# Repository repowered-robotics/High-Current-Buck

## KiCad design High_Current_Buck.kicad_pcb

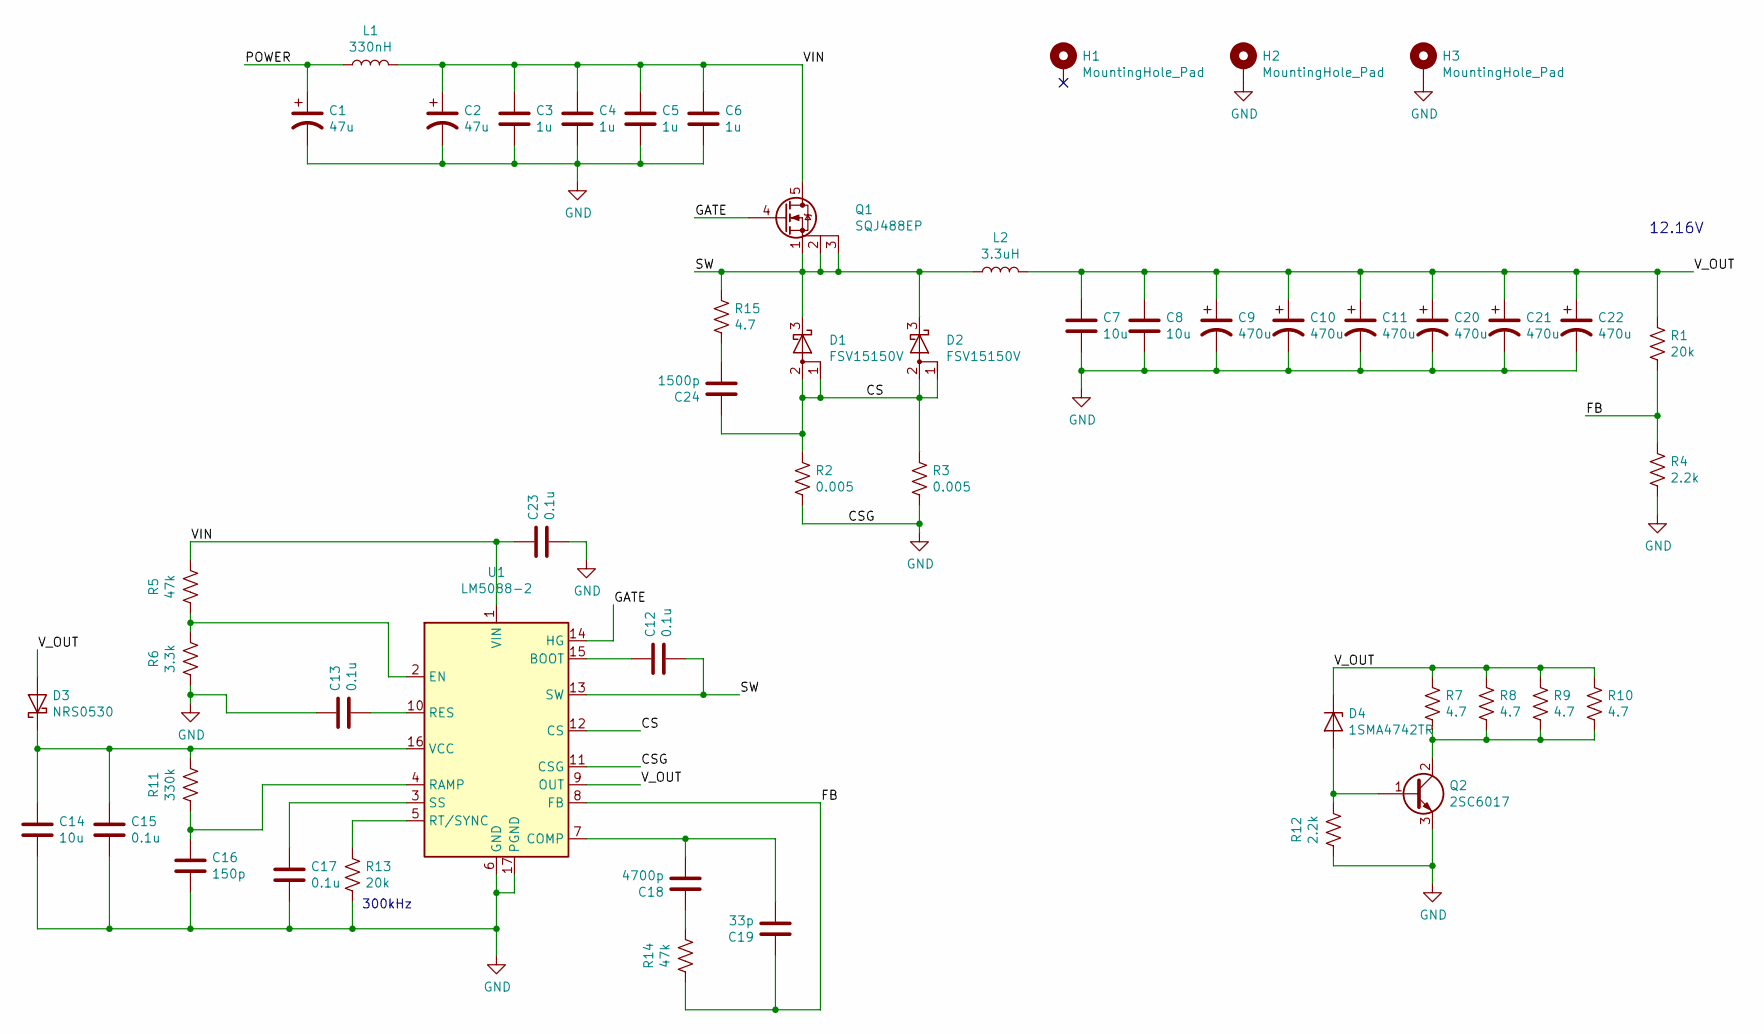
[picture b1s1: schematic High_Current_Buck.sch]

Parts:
C1, C2: 47u; CP_Radial_D12.5mm_P5.00mm
C3, C4, C5, C6: 1u; C_1206_3216Metric
C7, C8, C14: 10u; C_1206_3216Metric
C9, C10, C11, C20, C21, C22: 470u; CP_Radial_D12.5mm_P5.00mm
C12: 0.1u; C_0805_2012Metric
C13, C15, C17, C23: 0.1u; C_0603_1608Metric
C16: 150p; C_0603_1608Metric
C18: 4700p; C_0603_1608Metric
C19: 33p; C_0603_1608Metric
C24: 1500p; C_0805_2012Metric
D1, D2: FSV15150V; TO-277A
D3: NRS0530; D_SOD-323
D4: 1SMA4742TR; D_SMA
H1, H2, H3: MountingHole_Pad; MountingHole_3.7mm_Pad
L1: 330nH; L_Vishay_IHLP-3232
L2: 3.3uH; L_Wuerth_HCI-2212
Q1: SQJ488EP; PowerPAK_SO-8L_Single
Q2: 2SC6017; TO-252-2
R1, R13: 20k; R_0603_1608Metric
R2, R3: 0.005; R_2512_6332Metric
R4, R12: 2.2k; R_0603_1608Metric
R5, R14: 47k; R_0603_1608Metric
R6: 3.3k; R_0603_1608Metric
R7, R8, R9, R10, R15: 4.7; R_2512_6332Metric
R11: 330k; R_0603_1608Metric
U1: LM5088-2; HTSSOP-16-1EP_4.4x5mm_P0.65mm_EP3.4x5mm_Mask3x3mm_ThermalVi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

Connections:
/CS: C24.1, D1.1 (A), D1.2 (A), D2.1 (A), D2.2 (A), R2.1, R3.1, U1.12 (CS)
/FB: C19.1, R1.2, R4.1, R14.1, U1.8 (FB)
/GATE: Q1.4 (G), U1.14 (HG)
/POWER: C1.1, L1.1
/SW: C12.2, D1.3 (K), D2.3 (K), L2.1, Q1.1 (S), Q1.2 (S), Q1.3 (S), R15.1, U1.13 (SW)
/VIN: C2.1, C3.1, C4.1, C5.1, C6.1, C23.1, L1.2, Q1.5 (D), R5.2, U1.1 (VIN)
/V_OUT: C7.1, C8.1, C9.1, C10.1, C11.1, C20.1, C21.1, C22.1, D3.2 (A), D4.1 (K), L2.2, R1.1, R7.1, R8.1, R9.1, R10.1, U1.9 (OUT)
GND: C1.2, C2.2, C3.2, C4.2, C5.2, C6.2, C7.2, C8.2, C9.2, C10.2, C11.2, C13.1, C14.2, C15.2, C16.2, C17.2, C20.2, C21.2, C22.2, C23.2, H2.1, H3.1, Q2.3 (E), R2.2, R3.2, R4.2, R6.1, R12.1, R13.2, U1.6 (GND), U1.11 (CSG), U1.17 (PGND)
unnamed: C12.1, U1.15 (BOOT)
unnamed: C13.2, U1.10 (RES)
unnamed: C14.1, C15.1, D3.1 (K), R11.2, U1.16 (VCC)
unnamed: C16.1, R11.1, U1.4 (RAMP)
unnamed: C17.1, U1.3 (SS)
unnamed: C18.1, R14.2
unnamed: C18.2, C19.2, U1.7 (COMP)
unnamed: C24.2, R15.2
unnamed: D4.2 (A), Q2.1 (B), R12.2
unnamed: Q2.2 (C), R7.2, R8.2, R9.2, R10.2
unnamed: R5.1, R6.2, U1.2 (EN)
unnamed: R13.1, U1.5 (RT/SYNC)

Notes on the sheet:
300kHz
12.16V

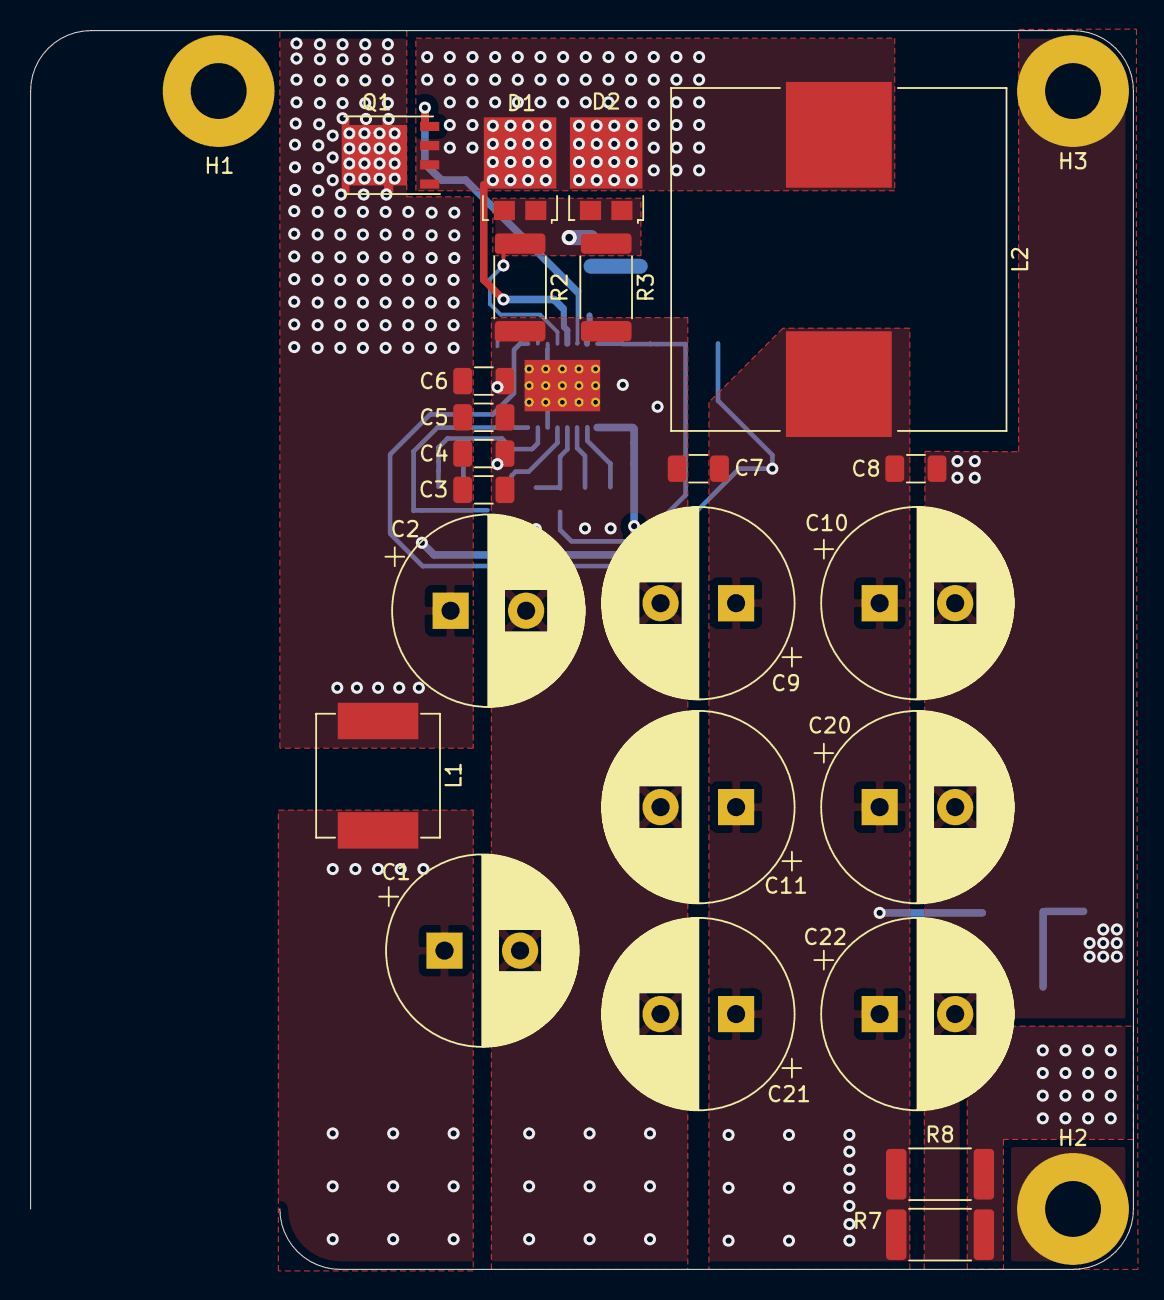
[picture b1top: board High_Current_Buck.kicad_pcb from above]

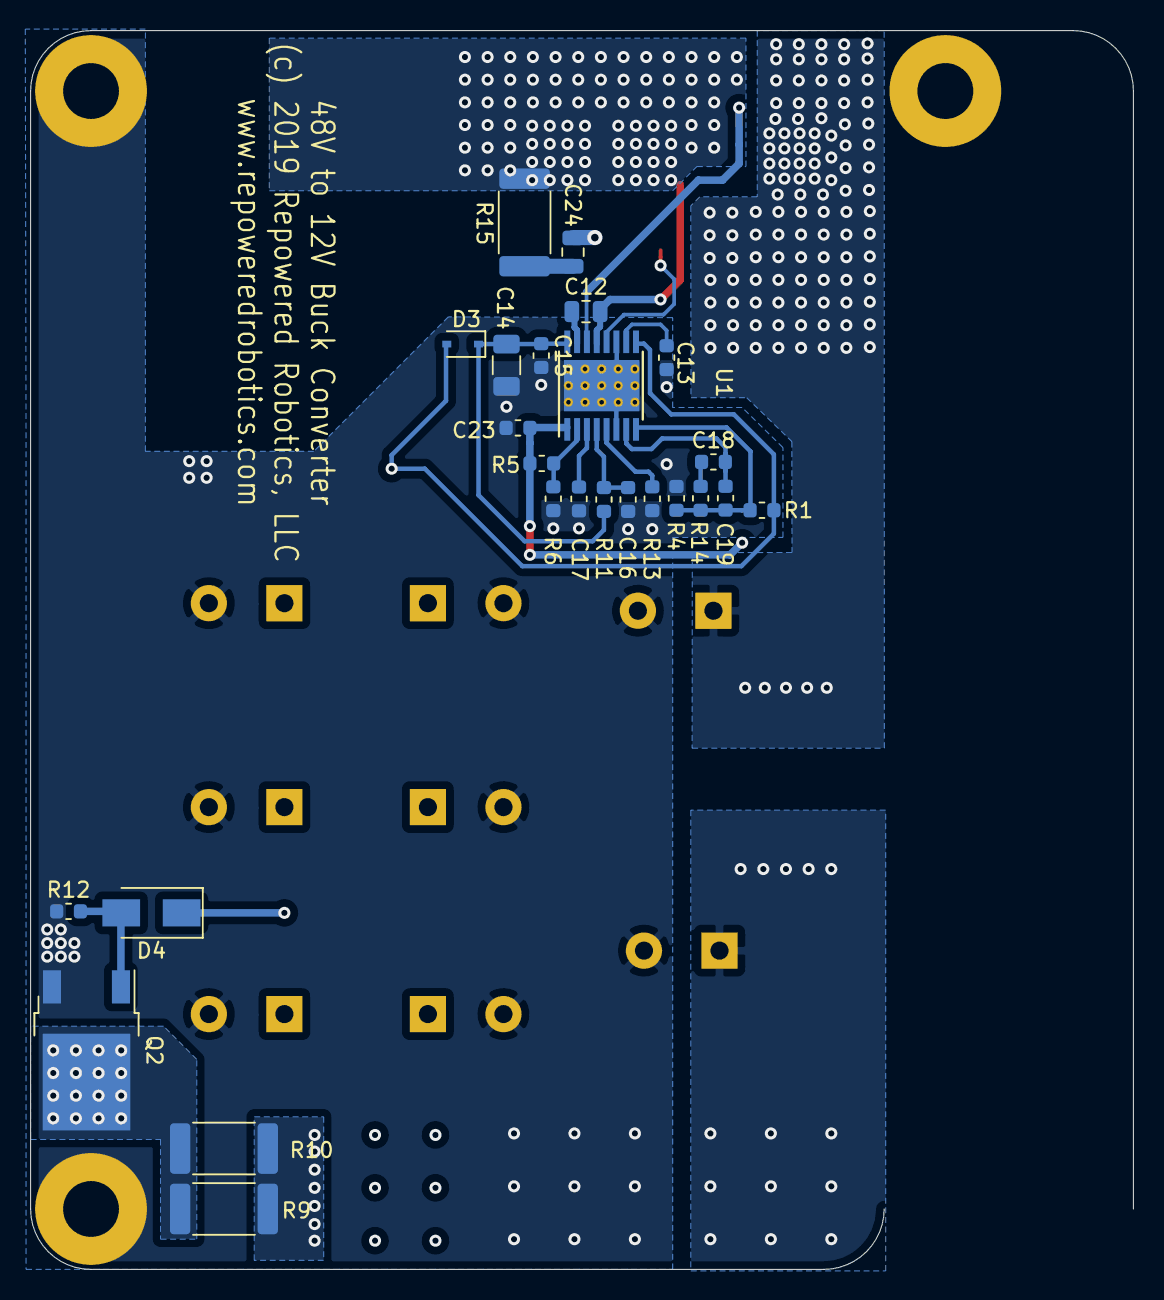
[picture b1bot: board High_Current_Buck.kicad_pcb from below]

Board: 2 copper layers, 73.0 x 82.0 mm, 51 parts (25 on the bottom side), 20 nets.

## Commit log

2019-10-23 Add files for first production run
2019-11-06 begin some changes to thermal dissipation area
2019-11-06 Add step file

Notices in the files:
High_Current_Buck.kicad_pcb:
(c) 2019 Repowered Robotics, LLC
